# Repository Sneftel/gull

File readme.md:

# Gull

**NOTE:** These images are from Gull V1. V2 is quite similar, but the thumb cluster attaches to the rib rather than being a part of it.

Gull is a dished ergonomic keyboard. It contains no 3D-printed parts and no hand-wired circuitry, and is designed for rapid constructibility rather than aesthetics. Keys are inserted into thin FR4 PCBs which are bent to the frame.

The raison d'etre of Gull is to be rapidly assembled, tweaked, and remade. The frame is fully parameterized, and changing a parameter generally only requires recutting one shape. PCBs can be reused after changing almost any parameters. The exposed ribbon cables make it potentially impractical for portable use.

The key layout is essentially 3x6 on each side. There are six additional keys per side, two in the bottom center of each side and four (relatively inaccessible) keys at the top corners of each side.

PCB layout is in KiCad. Frame shapes are in OpenSCAD. The firmware is QMK; the fork is available at https://github.com/Sneftel/qmk_firmware/tree/gull , and will be PR'd back when I get some time to clean it up.

## Tools

The frame for Gull must be cut from acrylic or similar using a laser cutter.

The PCBs have surface-mount components. A hotplate is the best tool for soldering these, but hand soldering is also possible. Hot air reflow can be used but be aware of temperature limits for the FFC connectors.

Good tweezers are useful for working with the FFC cables, particularly with SOWgull.

## Materials

I use six millimeter-thick acrylic for the frame. Eight millimeter will also work. Below six millimeters is not recommended. Plywood will likely also be acceptable, though I have not tested the most recent shapes with plywood.

The finger and thumb PCBs should be fabricated from 0.8mm-thick FR4. I have not tested other materials or thicknesses. The center PCB should be fabricated from thicker FR4 (I use standard 1.6mm-thick FR4).

## Parts

The following parts are required:

### Hardware 

* 38 14mm-long M3 bolts (not countersunk)
* 26 10mm-long M3 bolts (not countersunk)
* 56 M3 square nuts. I used 6mm width, 2mm thickness, but other sizes will also work.
* 4 4mm female-threaded hex spacers
* 2 20mm female-threaded hex spacers for each bending clamp (optional, discussed below)
* 4 M3 hex nuts

### Components

* 56 Kailh Choc V1 low-profile keyswitches
* 56 Choc V1 keycaps
* 56 0805 diodes
* 16 vertical FFC connectors, 10 pin, 0.5mm pitch. I used GCT FFC2A33 connectors. Other brands will likely work, but check that the land pattern is roughly equivalent. In particular, check that the upper pins are skewed right of the lower pins.
* 8 FFC ribbon cables in various lengths from 10cm to 25cm, 10pin, 0.5mm pitch. I used type B (opposite side contacts) because that gives more flexibility to orient them with the marked side hidden, but type A will also work.
* Pins and sockets for a Pro Micro MCU
* Pro Micro MCU (or pinout-compatible)

### Laser-cut pieces

* 6 ribs, 2 for each position
* 4 spines
* 2 thumb cluster necks
* 2 thumb cluster bodies
* 12 stabilizers
* 1 pelvis
* 2 bending clamps for each distinct rib radius (optional, discussed below)

### PCBs

* 6 fingerboards, in 0.8mm FR4
* 2 thumbboards, in 0.8mm FR4
* 1 centerboard, in 1.6mm FR4 or similar

## Customization

### Basic development

Most customization should be done through frame/params.scad. This file contains almost all parameters one might want to tweak, and documents which pieces are affected by which parameters. 

To visualize the keyboard as a whole, open frame/main.scad. This file should not be used to generate shapes for laser cutting.

### Dilation

The OpenSCAD files dilate some parts to account for the laser cutter's kerf. If your cutter's control software includes this as a feature, you should either disable it in the control software, or disable the dilation by setting the KERF parameter in params.scad to 0. Otherwise, cut a 10mm square, measure the average of its side lengths and subtract that from 10, and set KERF to that value. If the kerf is above 0.6 or so, you may have trouble getting things to fit firmly.

### Customizing the T-slots

For easy assembly, it's useful for the square nuts to firmly friction-fit into the T-slots. This requires a fairly tight tolerance. The "tnuttester.scad" file can be used to empirically determine the right parameters for this, given a particular laser cutter and material. See the comments in that file for how to use it.

### Customizing the bending clamp

If you have customized the rib radii, you will need to customize the bending clamp radius to match (the parameter BEND_RADIUS in clamp.scad), and you will need to fabricate separate clamp shapes for each distinct rib radius. 

## Fabrication

### PCBs

The fingerboards and centerboard may be panelized or printed as-is. To build Gerber files which should be acceptable at most fabs (I use Elecrow), run makeall.bat or "make" in the board directory.

The thumbboard has delicately narrow areas and should be carefully panelized for fabrication. I use KiKit for this, with "panelize.json" containing the necessary presets. The auto-built Gerbers are panelized in this way. Make sure to mention the need for V-cuts to the PCB fabricator. Mousebites would also work.

The center FFC connector on the centerboard, just below the MCU, is for future expansion and does not need to be populated.

### Laser-cut shapes

Execute "make svg" or (on Windows) "makeall.bat svg" to generate SVG shapes for all laser-cut pieces. DXF and PDF outputs are also supported.

I use Deepnest.io to nest the pieces for printing. Consider manually nesting the stabilizers and printing them separately.

The OpenSCAD files dilate some parts to account for laser-cut kerf. See the discussion of kerf in the "customization" section.

## Assembly

Follow the following steps for assembly:

### Solder the PCBs

The thumbboards should remain panelized until after both SM and TH components are soldered. 

Solder only one connector per thumbboard: J1 on one, J2 on the other. The thumb cluster switches will be on the opposite side from the connector.

The FFC connectors have pin 1 indicators that are subtle at best. Make sure to solder them consistently; the connections will work when reversed if the column pin mapping is reversed.

### Assemble the frame

It's marginally easier to do this before attaching the thumb and finger PCBs. First attach the spines to the pelvis, then the ribs to the spine. (You will use only the 14mm bolts for these.)

Ideally, the square nuts can be press-fit into the T-slots and will stay there for assembly. If a fit is too loose or tight, try a different nut, or try rotating the nut. A drop of glue, or a piece of tape, can also be used to keep things in position.

### Assemble the bending clamp

The shapes include a clamp for use when mounting the fingerboards to the ribs. You can insert each fingerboard into the clamp (keys towards the clamp) and bend and hold it in place with one hand. This makes it easier to bolt it down. 

However, this clamp requires 20mm spacers, which you otherwise wouldn't need, so you can keep your BOM down a bit by bending the fingerboards without one; this option is discussed below.

To assemble the clamp, insert a 10mm bolt in each hole and screw down to a 20mm spacer on the other side. Then put the other clamp on the other side of the spacers and bolt to the spacers with two more 10mm bolts.

### Mount fingerboards

If you have the bending clamp: Insert a fingerboard all the way into the back of the clamp (the FFC connector will be towards the back, and facing the curved surfaces of the clamp), place a stabilizer on the fingerboard (under the hooks at the end) and bend and hold it to the curve with your non-dominant hand.  Use your other hand to insert the bolts and screw them down, inserting a second stabilizer on the other side as you do so. Then tighten everything down and adjust the stabilizers.

If you don't have the bending clamp: It's easiest to mount the fingerboards with two people, one bending the board to the frame and one inserting the 10mm bolts. Failing that, bend in as well as possible and attach the center bolt but do not fully tighten it. Then insert a stabilizer on each side (it will not yet fit firmly). Continue to bend and attach the other two bolts, then tighten everything down and adjust the stabilizers.

### Mount thumbboards

Break off the frames. Fit square nuts into the thumb cluster bodies for later. 

The thumb cluster PCBs should have the connector facing away from the user; swap left and right if this is not the case. Carefully bend the row of three keys to insert into the body of the thumb cluster, with the PCB inserted from the same side as the T-slot is on. Go slow and make sure the PCB is slotting in correctly. The fit should be firm but there should be no need to force anything.

Then attach the necks. Both will slide in from the bottom. Bolt the necks in while checking for centered and square positioning. Then attach the thumb clusters to the rest of the frame.

### Mount centerboard

Attach four 14mm bolts from the top of the centerboard and secure finger-tight with the 4mm spacers on the bottom. Insert the bolt shanks through the holes in the pelvis and secure with nuts.

### Attach cables and microcontroller.

Insert and secure FFC ribbon cables in the centerboard one by one, fishing them through the frame and inserting them into the fingerboards and thumbbboards. Take care they are oriented properly, and if desired reverse them so the printing is on a consistent side. The thumb cluster cables must be connected to the two side connectors closest to the user. The other cables are intended to be connected with the outermost fingerboards on the connectors further from the user, but row pins can be remapped to compensate if they are connected differently.

Finally, insert the microcontroller. (It's easiest to do this last, so there's more room to connect the cables.)

### Fix row/column mappings

There's a decent chance that the row/column mappings in info.json won't be correct, depending on which FFC cables you used and how you mounted the connectors. If you add 

## SOWGull

SOWGull is a split variant of Gull, with a 3.5mm audio cable used to connect the halves.

Most of SOWGull is the same as a normal Gull, and it is easy to convert a Gull into a SOWGull (or vice versa). Only the centerboard and pelvis differ.

### Parts

The BOM has the following differences:

* PCBs: Two SOW boards instead of one centerboard.
* Laser-cut shapes: Two sowpelvis shapes instead of one pelvis shape.
* Hardware: Two additional 10mm-long M3 bolts, two additional 4mm hex spacers, and two additional hex nuts.
* Components: Two PJ-320A 3.5mm TRRS jacks; two Pro Micro boards instead of one; a TRS or TRRS cable for connection.

### Assembly

The SOW board is a reversible PCB. The microcontroller board should be mounted with the USB port facing away from the user, and as far away as possible from the user (with four through-holes towards the user left unused). The TRRS jack is mounted closer to the user.

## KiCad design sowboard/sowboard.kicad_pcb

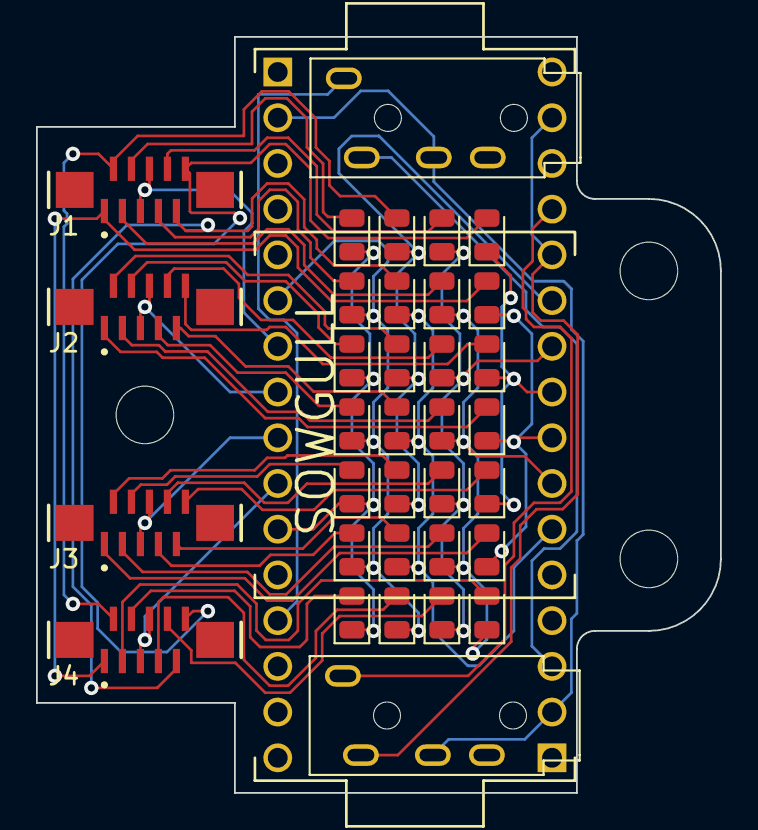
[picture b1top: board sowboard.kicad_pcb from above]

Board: 2 copper layers, 38.0 x 42.0 mm, 35 parts (0 on the bottom side), 45 nets.

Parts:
D1, D2, D3, D4, D5, D6, D7, D8, D9, D10, D11, D12, D13, D14, D15, D16, D17, D18, D19, D20, D21, D22, D23, D24, D59, D60, D61, D62: 1N4148W; D_0805_2012Metric
J1, J2, J3, J4: Conn_01x10_MountingPin; GCT_FFC2A33-10-T-R_REVA
U1: ProMicro; ProMicro-Rotatable
U2, U3: PJ-320A

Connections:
/Column L1/R1: D1.2 (A), J1.1, J4.1
/Column L1/R2: D2.2 (A), J1.2, J4.2
/Column L1/R7: D7.2 (A), J1.9, J4.9
/Column L1/R8: D8.2 (A), J1.10, J4.10
/Column L2/R1: D9.2 (A), J2.1
/Column L2/R2: D10.2 (A), J2.2
/Column L2/R7: D15.2 (A), J2.9
/Column L2/R8: D16.2 (A), J2.10
/Column L3/R1: D17.2 (A), J3.1
/Column L3/R2: D18.2 (A), J3.2
/Column L3/R7: D23.2 (A), J3.9
/Column L3/R8: D24.2 (A), J3.10
COL_L1: J1.5, J1.6, U1.7 (D4)
COL_L2: J2.5, J2.6, U1.8 (C6)
COL_L3: J3.5, J3.6, U1.9 (D7)
COL_T: J4.5, J4.6, U1.10 (E6)
unnamed: D3.2 (A), J1.3
unnamed: D4.2 (A), J1.4
unnamed: D5.2 (A), J1.7
unnamed: D6.2 (A), J1.8
unnamed: D11.2 (A), J2.3
unnamed: D12.2 (A), J2.4
unnamed: D13.2 (A), J2.7
unnamed: D14.2 (A), J2.8
unnamed: D19.2 (A), J3.3
unnamed: D20.2 (A), J3.4
unnamed: D21.2 (A), J3.7
unnamed: D22.2 (A), J3.8
unnamed: D59.2 (A), J4.3
unnamed: D60.2 (A), J4.4
unnamed: D61.2 (A), J4.7
unnamed: D62.2 (A), J4.8
unnamed: U1.20 (F4), U1.23 (GND), U3.2 (Tip)
unnamed: U1.2 (RX), U1.2B (RX), U2.3 (Ring1), U3.3 (Ring1)
unnamed: U1.21B (VCC), U2.1 (Sleeve)
unnamed: U1.3B (GND), U2.2 (Tip)
unnamed: U1.21 (VCC), U3.1 (Sleeve)
ROW_1: D1.1 (K), D9.1 (K), D17.1 (K), U1.16 (B1)
ROW_2: D2.1 (K), D10.1 (K), D18.1 (K), U1.19 (F5)
ROW_3: D3.1 (K), D11.1 (K), D19.1 (K), D59.1 (K), U1.15 (B3)
ROW_4: D4.1 (K), D12.1 (K), D20.1 (K), D60.1 (K), U1.11 (B4)
ROW_5: D5.1 (K), D13.1 (K), D21.1 (K), D61.1 (K), U1.6 (SCL)
ROW_6: D6.1 (K), D14.1 (K), D22.1 (K), D62.1 (K), U1.18 (F6)
ROW_7: D7.1 (K), D15.1 (K), D23.1 (K), U1.14 (B2)
ROW_8: D8.1 (K), D16.1 (K), D24.1 (K), U1.17 (F7)

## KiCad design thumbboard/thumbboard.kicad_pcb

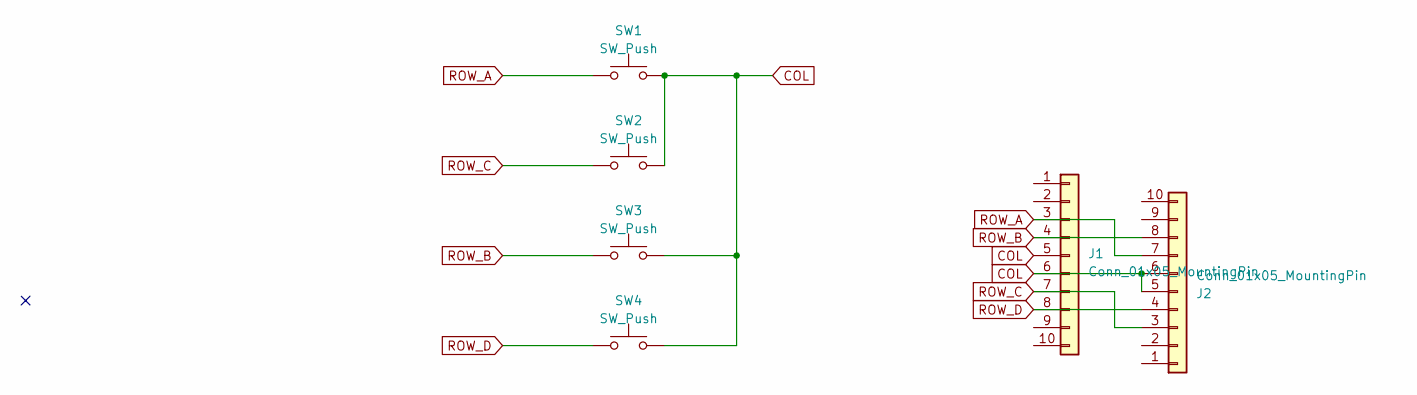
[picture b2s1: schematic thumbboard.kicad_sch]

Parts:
J1: Conn_01x05_MountingPin; GCT_FFC2A33-10-T-R_REVA_Clipped1
J2: Conn_01x05_MountingPin; GCT_FFC2A33-10-T-R_REVA_Clipped2
SW1, SW3, SW4: SW_Push; SW_PG1350_reversible
SW2: SW_Push; SW_PG1350_reversible_MissingCorner

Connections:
COL: J1.5, J1.6, J2.5, J2.6, SW1.1, SW2.1, SW3.1, SW4.2
ROW_A: J1.3, J2.7, SW1.2
ROW_B: J1.4, J2.8, SW3.2
ROW_C: J1.7, J2.3, SW2.2
ROW_D: J1.8, J2.4, SW4.1

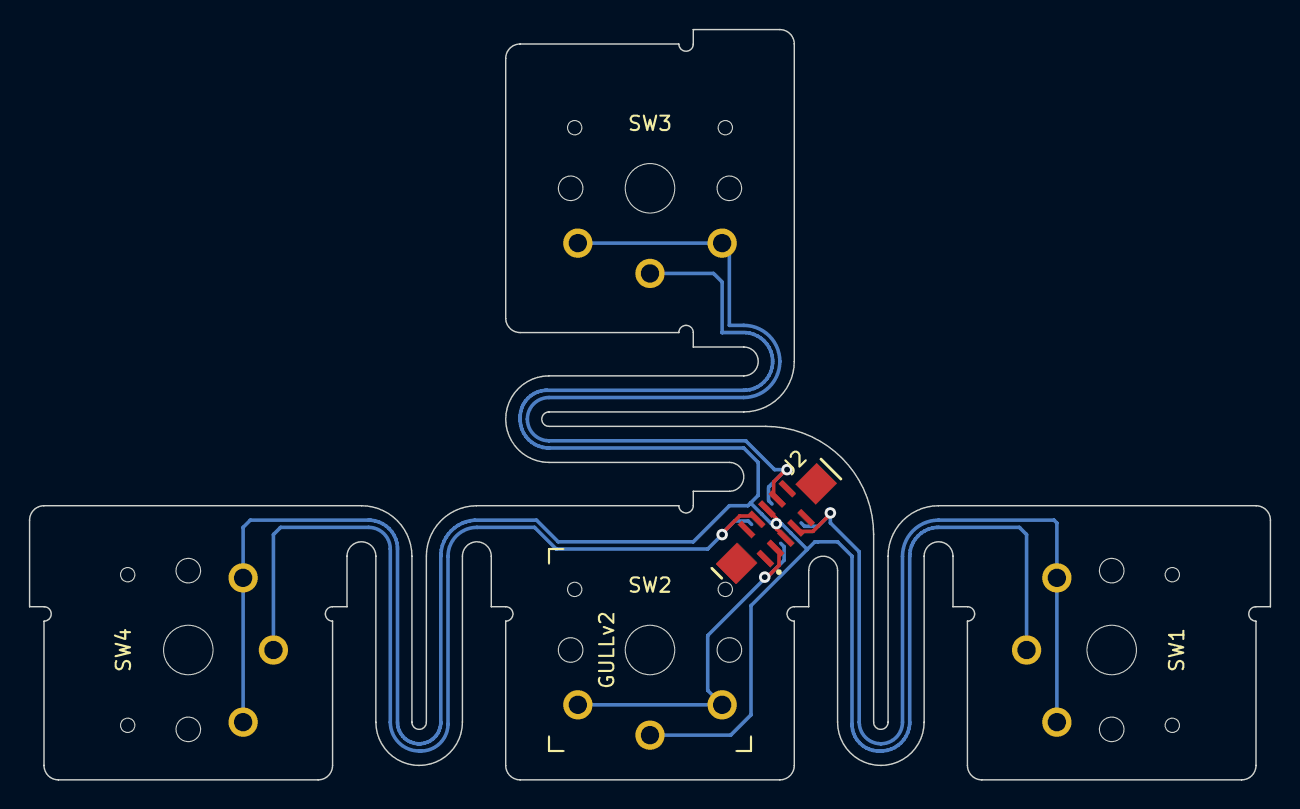
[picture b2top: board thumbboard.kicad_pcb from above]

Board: 2 copper layers, 86.0 x 52.0 mm, 12 parts (1 on the bottom side), 5 nets.

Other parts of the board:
T1, T2, T3, T4, T4#2, T4#3: Tab

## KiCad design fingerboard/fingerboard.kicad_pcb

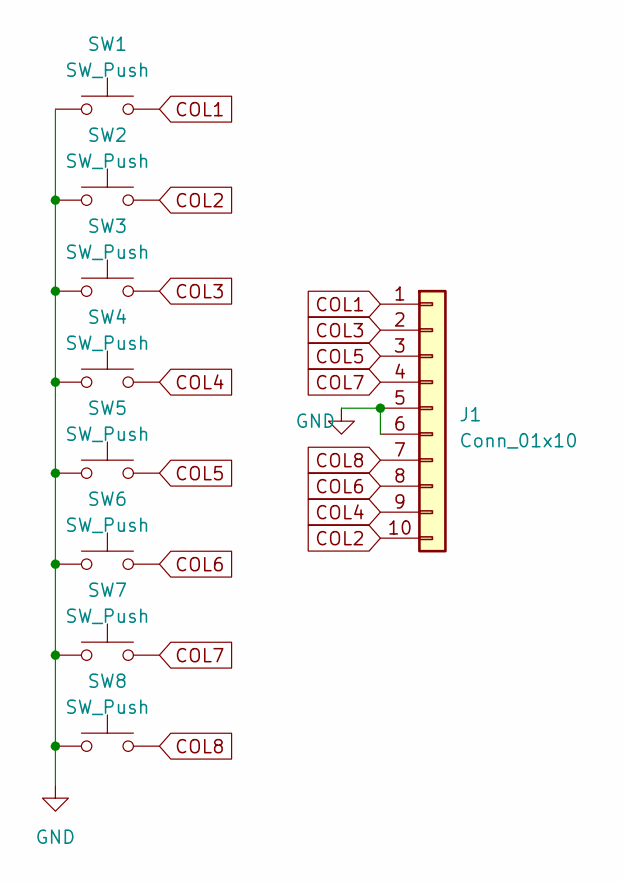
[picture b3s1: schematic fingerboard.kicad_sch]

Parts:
J1: Conn_01x10; TE_1-1734839-0_1x10-1MP_P0.5mm_Horizontal
SW1, SW2, SW3, SW4, SW5, SW6, SW7, SW8: SW_Push; SW_PG1350

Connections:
COL1: J1.1, SW1.2
COL2: J1.10, SW2.1
COL3: J1.2, SW3.2
COL4: J1.9, SW4.1
COL5: J1.3, SW5.2
COL6: J1.8, SW6.1
COL7: J1.4, SW7.2
COL8: J1.7, SW8.1
GND: J1.5, J1.6, SW1.1, SW2.2, SW3.1, SW4.2, SW5.1, SW6.2, SW7.1, SW8.2

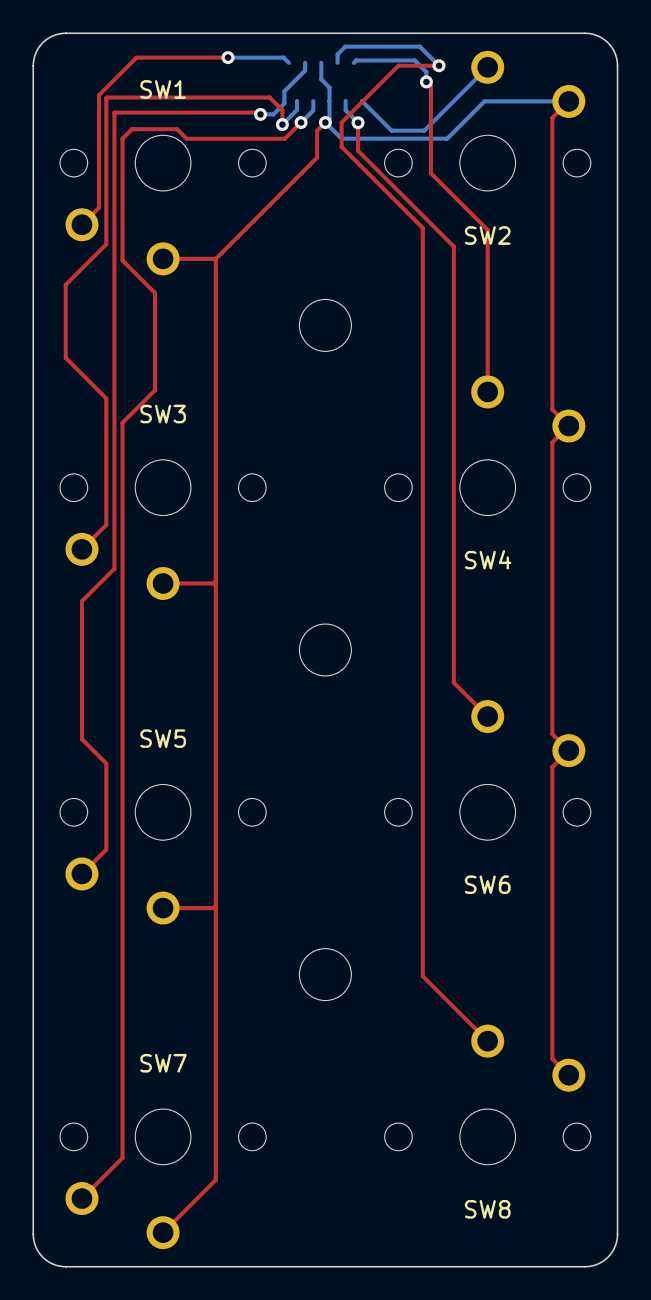
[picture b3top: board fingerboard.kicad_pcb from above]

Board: 2 copper layers, 36.0 x 76.0 mm, 9 parts (1 on the bottom side), 9 nets.

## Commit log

2023-12-13 Initial import
2023-12-13 add ignore file
2023-12-13 tweaks and variable renames
2023-12-14 Lots of tweaks
2023-12-14 rename "paddle" to "pcb" when referring to tc pcb rather to than the individual paddles
2023-12-16 Fix loc of rib foot
2023-12-16 Allow actual thickness to diverge from nominal in rendering
2023-12-16 Add cable guides; render ribs in main through instantiations to reduce codedup
2024-01-07 Add stabilizers
2024-01-07 Add PN; use it in pelvis
2024-01-07 A hack to adjust material thickness without adjusting the PCB (which was designed for 8mm in thumb cluster)
2024-01-07 Reduce magic numbers in TC
2024-01-07 Tweak some params
2024-01-07 Add thumbboard
2024-01-09 Add finger board
2024-01-13 add centerboard
2024-01-13 Major refactor: Add anchor capabilities to PN; use PN for remaining parts; refactor main to use anchors to position things
2024-01-13 Simplify anchoring strategy
2024-01-15 Various refactorings. Add fingerboard pcb visualization to main.
2024-01-15 code style
2024-01-15 finish refactoring TC to use PN (still needs some cleanup)
2024-01-15 recolor stabilizers
2024-01-15 mild refactoring of tcbody
2024-01-22 redo centerboard again (and again)
2024-01-22 complete thumbboard; increase arclength and sharpen angle
2024-01-22 whole bunch of uncategorized changes
2024-01-22 update/add gitignores
2024-01-27 Fix Rect impl, add support for EXTRA in Rect
2024-01-27 fix gitignore
2024-01-27 Change naming, misc tweaks, add connector cutout back
2024-01-27 Reduce the height by 15mm (!)
2024-01-27 Raise mockup to sit on XY plane
2024-02-01 Add label to thumbboard; make bottom tabs narrower (hard to break off the frame without damaging the thing)
2024-02-01 Overhaul T-slots a bit and make them (and the bolts) longer
2024-02-01 add testing tool to find ideal T-nut thickness
2024-02-01 add comments
2024-02-01 remove and ignore kicad local settings files
2024-02-02 Improve the tnuttester to find both width and depth
2024-02-03 Tidy up tccommon with Rect; add space in ends of TC PCB guides to improve cutting and ease depanelling; slightly thicken TC features which were deforming and breaking
2024-02-03 small aesthetic tweaks
2024-02-03 misc cleanups
2024-02-03 fix swapped front/back centerboard hole widths (oops)
2024-02-03 overhaul TC PCB guide rails again a bit
2024-02-03 widen cable guide slots to help clear offcuts
2024-02-03 Add corner cutouts to interconnects, so pieces sit flat instead of fulcruming at the shared corner
2024-02-03 Swap x/y in Rect anchor names
2024-02-03 Add "washer" rings around interconnect bolt holes for more even support
2024-02-03 Add kerf correction (not sure if this is a good idea)
2024-02-03 give the thumb boards just a little bit more room
2024-02-04 Standardize and improve cleared corner cutouts
2024-02-07 Testing and tweaking; added channels to tnuttester to get the test holes closer to the real holes
2024-02-07 give bolts a bit more room
2024-02-08 Fix T-slot lengths
2024-02-08 Applying results from destructive testing: Make pelvis/spine and spine/rib interconnect lengths independent; lengthen the former; make pelvis wider to make room, move ribs in to compensate
2024-02-08 shorten fingerboard bolts
2024-02-08 Fix positioning in main.scad when actual thickness varies from nominal thickness
2024-02-14 reduce saturation of a preview color
2024-02-14 cleanup
2024-02-14 Make TC a bit hardier
2024-02-14 tweak TC positioning a bit
2024-02-14 Flip riser for outer ribs to ease assembly
2024-02-14 Add cable guides in ribs to keep cables closer to the frame
2024-02-14 Remove cable guide from outer rib support (no longer needed now that spine's guide is on the other side)
2024-03-24 Rework centerboard yet again. Now with vertical FFC headers and a ground pour.
2024-03-24 spine-trunked FFCs
2024-03-24 fix cable guide dimension calculation
2024-03-24 shorten cable guides a bit (still longer than before the previous fix); lengthen fingerboard bolts to 10mm
2024-03-26 add a bit of extra height to stabilizers (should probably do this with dilation)
2024-03-26 rearrange and add documentation to params
2024-03-27 Move and document TC attachment parameters
2024-04-12 partial readme
2024-04-12 reformat a bit
2024-04-12 more documentation
2024-04-15 clarify connector situation
2024-04-15 reformat
2024-04-28 First V2 work: Add a separate TC body piece, attached to the neck which is in turn attached to the rib. Also add positive geometry around interconnects (to help with debugging placement, mostly)
2024-04-28 Tweaks and cleanups. Still need to clean some stuff up and pull out/organize/rename params, and probably remove old params
2024-04-28 Add some redundant traces to centerboard to fix benign DRC violations
2024-04-28 Make thumbboard reversible; move connector
2024-04-28 Overhaul fingerboard (incl vertical connector)
2024-04-28 add some makeall.bat files for PCBs
2024-04-28 Consolidate and improve gitignores
2024-04-29 Swap TC body orientation (still haven't decided which is better)
2024-04-29 Comment out test code
2024-04-29 Some more TC measurement tweaks and cleanups (still needs work).
2024-04-29 Update the readme a bit
2024-04-29 remove forward rib edge to make room for vertical connector. Still some naked constants to pull out.
2024-04-29 Add tcbody to makefile/makeall.bat. Overhaul makefile a little for deps and readability. Also remove spurious dep of rib on tccommon, and update gitignore.
2024-04-29 Flip the rib-TC attachment to allow for lower TCs
2024-04-29 More TC work: cleanups, swapping interconnect directions again, pulling out and documenting parameters. Also getting rid of dead code.
2024-04-29 Add positive support region around the nut in T-slots (in all parts, but only relevant to the TC for now)
2024-04-29 cleanups
2024-04-30 update readme again
2024-04-30 remove outdated warning from readme
2024-04-30 add images to readme
2024-04-30 Add top-level makeall (windows only for now)
2024-04-30 clear stale frame files during build
2024-04-30 recolor tcbody in main.scad to add contrast
2024-04-30 update readme for current PCB fab instructions
2024-05-01 Add toggle for corner clearing
2024-05-06 make makefiles/makealls a bit cleaner; add top-level makefile
2024-05-06 overhaul a few things for readability; add pn_pospos() to preserve bumpers in all T-slots
2024-05-06 add clamp tool for use when bending fingerboards
2024-05-06 add non-slipping contact to endhook
2024-05-06 Add clearance below the keywell underneath the endhook in the clamp, to make it possible to actually wedge the thing in there. Also move that bolt hole to the top of the endhook, for greater stabilit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
2024-05-06 discuss bending clamp in readme
2024-05-06 add better organization to the readme and mention the need to customize the bending clamp
2024-05-06 remove orphaned cleared corner
2024-05-06 prevent fingerboard from catching on clamp undercut
2024-05-06 deepen the undercut slightly
2024-05-07 Center fingerboard connector (fraction of a millimeter, not really a practical difference) and put grid origin somewhere useful
2024-05-07 Shorten rib leading edge slightly to make more room for FFC
2024-05-07 Put components on preview fingerboard
2024-05-10 Overhaul clamp a bit to grip both the fingerboard and one of its stabilizers
2024-05-11 Fix undercut positioning; increase overhang
2024-05-13 Mention the extra FFC connector
2024-05-13 Move silkscreen text to be less noticeable in final kb
2024-05-23 Initial version of SOWGull
2024-05-23 add sowgull info to readme
2024-05-23 add some details to the readme
2024-06-08 Make bending clamp a little easier to fit fingerboards into, and thin it out to make it easier to bolt down the fingerboards
2024-06-08 Move TCs inwards to improve keycap clearance
2024-06-08 add sowpelvis to makeall.bat
2024-06-08 param documentation
2024-06-08 improve TC/stabilizer clearance so the stabilizer sits more perpendicular
2024-06-08 Advise use of 20mm spacers for clamp instead of 15mm, now that I know it works
2024-06-08 Make the clamp look nicer. The *clamp*. Vanity, thy name is Ben.
2024-06-09 Increase clearance for audio plug
2024-06-15 Improve sowboard layout a bit, switch the data pin to PD2, and work around DRC warnings
2024-06-15 Edit readme, add sowgull image
2024-06-15 fix image filename
2024-06-15 properly round a couple corners on sowboard
2024-06-20 scoot the tc in a bit
